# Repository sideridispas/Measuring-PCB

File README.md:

# Measuring-PCB
Voltage, Current, Temperature and Timestamped measurement board with an Atmega328 as main CPU

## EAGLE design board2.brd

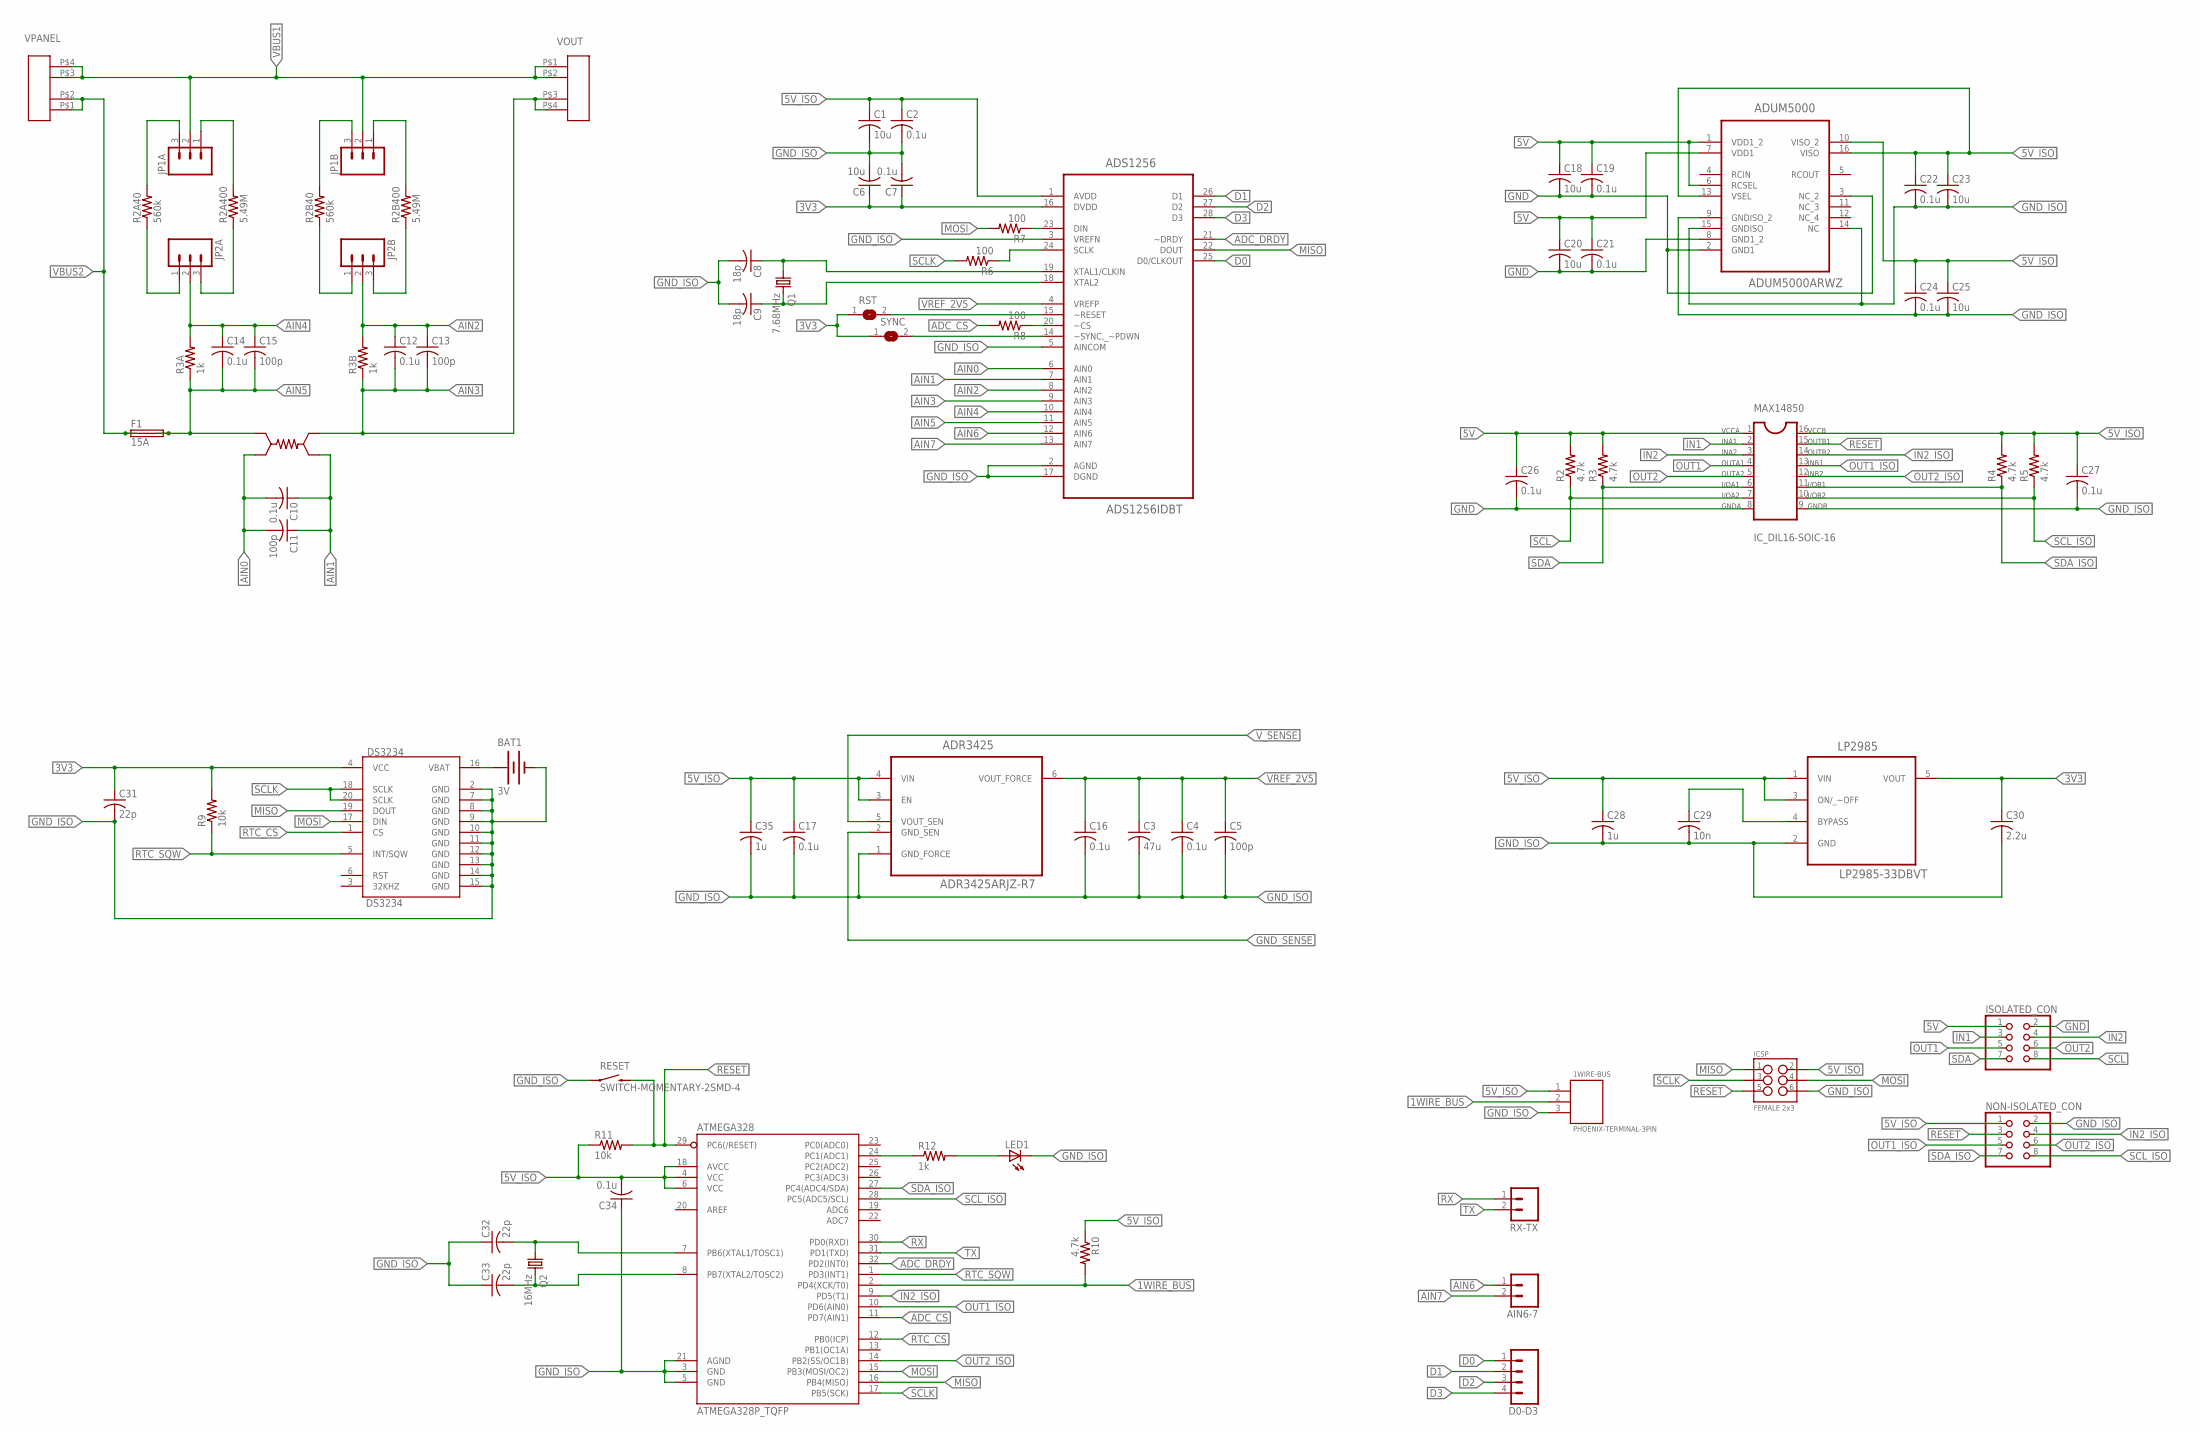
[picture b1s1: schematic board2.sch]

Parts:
1WIRE-BUS: PHOENIX-TERMINAL-3PIN
ADR3425: ADR3425ARJZ-R7; SOT95P280X145-6N
ADS1256: ADS1256IDBT; SOP65P780X200-28N
ADUM5000: ADUM5000ARWZ; SOIC127P1032X265-16N
AIN6-7: M021X02_NO_SILK; 1X02_NO_SILK
ATMEGA328: ATMEGA328P_TQFP; TQFP32-08
BAT1: 3V; BATTCON_12MM
C1, C6, C18, C20, C23, C25: 10u; C3216
C2, C4, C7, C10, C12, C14, C16, C17, C19, C21, C22, C24, C26, C27, C34: 0.1u; C3216
C3: 47u; C3216
C5, C11, C13, C15: 100p; C3216
C8, C9: 18p; C3216
C28, C35: 1u; C3216
C29: 10n; C3216
C30: 2.2u; C3216
C31, C32, C33: 22p; C3216
D0-D3: M04NO_SILK_ALL_ROUND; 1X04_NO_SILK_ALL_ROUND
DS3234: DS3234
F1: 15A; PAS_5X20
ICSP: FEMALE 2x3; 2X3
ISOLATED_CON: PINHD-2X4; 2X04
JP1A, JP1B, JP2A, JP2B: M03PTH; 1X03
LED1: LEDCHIPLED_0805; CHIPLED_0805
LP2985: LP2985-33DBVT; SOT95P280X145-5N
MAX14850: IC_DIL16-SOIC-16; SOIC-16
NON-ISOLATED_CON: PINHD-2X4; 2X04
Q1: 7.68MHz; HC49U-V
Q2: 16MHz; HC49U-V
R1: 0.005; LVK25
R2, R3, R4, R5, R10: 4.7k; R3216
R2A40, R2B40: 560k; M3216
R2A400, R2B400: 5.49M; M3216
R3A, R3B: 1k; M3216
R6, R7, R8: 100; R3216
R9, R11: 10k; R3216
R12: 1k; R3216
RESET: SWITCH-MOMENTARY-2SMD-4; TACTILE_SWITCH_TALL
RST: SJ
RX-TX: M02PTH; 1X02
SYNC: SJ
VOUT: PAS-PHOENIXTERMINAL2PIN-10.16MM; PAS-PHOENIXTERMINAL-2PIN-10.16MM
VPANEL: PAS-PHOENIXTERMINAL2PIN-10.16MM; PAS-PHOENIXTERMINAL-2PIN-10.16MM

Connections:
1WIRE_BUS: 1WIRE-BUS.2, ATMEGA328.2 (PD4(XCK/T0)), R10.2
3V3: ADS1256.16 (DVDD), C6.1, C7.1, C30.1, C31.1, DS3234.4 (VCC), LP2985.5 (VOUT), R9.2, RST.1, SYNC.1
5V: ADUM5000.1 (VDD1_2), ADUM5000.6 (RCSEL), ADUM5000.7 (VDD1), C18.1, C19.1, C20.1, C21.1, C26.1, ISOLATED_CON.1, MAX14850.1 (VCCA), R2.2, R3.2
5V_ISO: 1WIRE-BUS.1, ADR3425.3 (EN), ADR3425.4 (VIN), ADS1256.1 (AVDD), ADUM5000.10 (VISO_2), ADUM5000.13 (VSEL), ADUM5000.16 (VISO), ATMEGA328.4 (VCC), ATMEGA328.6 (VCC), ATMEGA328.18 (AVCC), C1.1, C2.1, C17.1, C22.1, C23.1, C24.1, C25.1, C27.1, C28.1, C34.2, C35.1, ICSP.2, LP2985.1 (VIN), LP2985.3 (ON/_~OFF), MAX14850.16 (VCCB), NON-ISOLATED_CON.1, R4.2, R5.2, R10.1, R11.1
ADC_CS: ATMEGA328.11 (PD7(AIN1)), R8.2
ADC_DRDY: ADS1256.21 (~DRDY), ATMEGA328.32 (PD2(INT0))
AIN0: ADS1256.6 (AIN0), C10.2, C11.2, R1.INV (2)
AIN1: ADS1256.7 (AIN1), C10.1, C11.1, R1.OUTV (4)
AIN2: ADS1256.8 (AIN2), C12.1, C13.1, JP2B.2, R3B.2
AIN3: ADS1256.9 (AIN3), C12.2, C13.2, R1.OUTI (3), R3B.1, VOUT.P$3, VOUT.P$4
AIN4: ADS1256.10 (AIN4), C14.1, C15.1, JP2A.2, R3A.2
AIN5: ADS1256.11 (AIN5), C14.2, C15.2, F1.2A, F1.2B, R1.INI (1), R3A.1
AIN6: ADS1256.12 (AIN6), AIN6-7.1
AIN7: ADS1256.13 (AIN7), AIN6-7.2
D0: ADS1256.25 (D0/CLKOUT), D0-D3.1
D1: ADS1256.26 (D1), D0-D3.2
D2: ADS1256.27 (D2), D0-D3.3
D3: ADS1256.28 (D3), D0-D3.4
GND: ADUM5000.2 (GND1), ADUM5000.3 (NC_2), ADUM5000.8 (GND1_2), C18.2, C19.2, C20.2, C21.2, C26.2, ISOLATED_CON.2, MAX14850.8 (GNDA)
GND_ISO: 1WIRE-BUS.3, ADR3425.1 (GND_FORCE), ADS1256.2 (AGND), ADS1256.3 (VREFN), ADS1256.5 (AINCOM), ADS1256.17 (DGND), ADUM5000.9 (GNDISO_2), ADUM5000.14 (NC), ADUM5000.15 (GNDISO), ATMEGA328.3 (GND), ATMEGA328.5 (GND), ATMEGA328.21 (AGND), BAT1.GND (-), C1.2, C2.2, C3.2, C4.2, C5.2, C6.2, C7.2, C8.2, C9.2, C16.2, C17.2, C22.2, C23.2, C24.2, C25.2, C27.2, C28.2, C29.2, C30.2, C31.2, C32.1, C33.1, C34.1, C35.2, DS3234.2 (GND), DS3234.7 (GND), DS3234.8 (GND), DS3234.9 (GND), DS3234.10 (GND), DS3234.11 (GND), DS3234.12 (GND), DS3234.13 (GND), DS3234.14 (GND), DS3234.15 (GND), ICSP.6, LED1.C, LP2985.2 (GND), MAX14850.9 (GNDB), NON-ISOLATED_CON.2, RESET.A2 (1)
GND_SENSE: ADR3425.2 (GND_SEN)
IN1: ISOLATED_CON.3, MAX14850.2 (INA1)
IN2: ISOLATED_CON.4, MAX14850.3 (INA2)
IN2_ISO: ATMEGA328.9 (PD5(T1)), MAX14850.14 (OUTB2), NON-ISOLATED_CON.4
MISO: ADS1256.22 (DOUT), ATMEGA328.16 (PB4(MISO)), DS3234.19 (DOUT), ICSP.1
MOSI: ATMEGA328.15 (PB3(MOSI/OC2)), DS3234.17 (DIN), ICSP.4, R7.2
unnamed: ADS1256.24 (SCLK), R6.1
unnamed: JP1A.3, R2A40.2
unnamed: JP1A.1, R2A400.2
unnamed: JP2A.3, R2A400.1
unnamed: JP2A.1, R2A40.1
unnamed: ATMEGA328.8 (PB7(XTAL2/TOSC2)), C33.2, Q2.2
unnamed: JP1B.3, R2B40.2
unnamed: JP1B.1, R2B400.2
unnamed: JP2B.3, R2B400.1
unnamed: JP2B.1, R2B40.1
unnamed: ADS1256.19 (XTAL1/CLKIN), C8.1, Q1.1
unnamed: ADS1256.18 (XTAL2), C9.1, Q1.2
unnamed: ATMEGA328.7 (PB6(XTAL1/TOSC1)), C32.2, Q2.1
unnamed: ADS1256.23 (DIN), R7.1
unnamed: BAT1.PWR@1 (+), DS3234.16 (VBAT)
unnamed: ADS1256.20 (~CS), R8.1
unnamed: ADS1256.15 (~RESET), RST.2
unnamed: ATMEGA328.24 (PC1(ADC1)), R12.1
unnamed: LED1.A, R12.2
unnamed: ADS1256.14 (~SYNC,_~PDWN), SYNC.2
unnamed: C29.1, LP2985.4 (BYPASS)
OUT1: ISOLATED_CON.5, MAX14850.4 (OUTA1)
OUT1_ISO: ATMEGA328.10 (PD6(AIN0)), MAX14850.13 (INB1), NON-ISOLATED_CON.5
OUT2: ISOLATED_CON.6, MAX14850.5 (OUTA2)
OUT2_ISO: ATMEGA328.14 (PB2(SS/OC1B)), MAX14850.12 (INB2), NON-ISOLATED_CON.6
RESET: ATMEGA328.29 (PC6(/RESET)), ICSP.5, MAX14850.15 (OUTB1), NON-ISOLATED_CON.3, R11.2, RESET.B2 (2)
RTC_CS: ATMEGA328.12 (PB0(ICP)), DS3234.1 (CS)
RTC_SQW: ATMEGA328.1 (PD3(INT1)), DS3234.5 (INT/SQW), R9.1
RX: ATMEGA328.30 (PD0(RXD)), RX-TX.1
SCL: ISOLATED_CON.8, MAX14850.7 (I/OA2), R2.1
SCLK: ATMEGA328.17 (PB5(SCK)), DS3234.18 (SCLK), DS3234.20 (SCLK), ICSP.3, R6.2
SCL_ISO: ATMEGA328.28 (PC5(ADC5/SCL)), MAX14850.10 (I/OB2), NON-ISOLATED_CON.8, R5.1
SDA: ISOLATED_CON.7, MAX14850.6 (I/OA1), R3.1
SDA_ISO: ATMEGA328.27 (PC4(ADC4/SDA)), MAX14850.11 (I/OB1), NON-ISOLATED_CON.7, R4.1
TX: ATMEGA328.31 (PD1(TXD)), RX-TX.2
VBUS1: JP1A.2, JP1B.2, VOUT.P$1, VOUT.P$2, VPANEL.P$3, VPANEL.P$4
VBUS2: F1.1A, F1.1B, VPANEL.P$1, VPANEL.P$2
VREF_2V5: ADR3425.6 (VOUT_FORCE), ADS1256.4 (VREFP), C3.1, C4.1, C5.1, C16.1
V_SENSE: ADR3425.5 (VOUT_SEN)

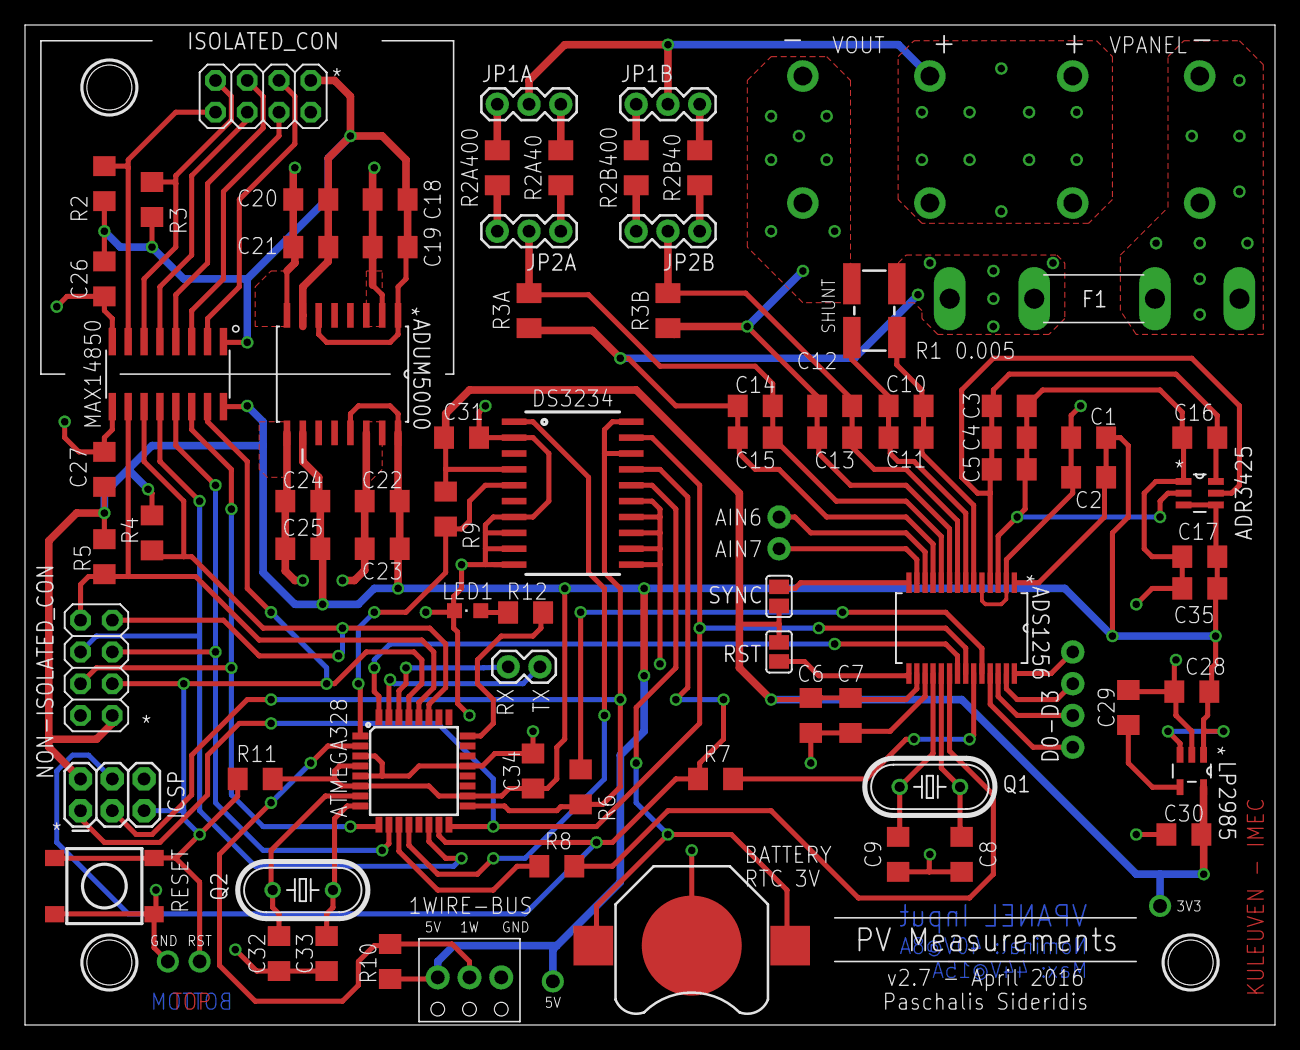
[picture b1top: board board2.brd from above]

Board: 2 copper layers, 100.0 x 80.0 mm, 81 parts (0 on the bottom side), 63 nets.

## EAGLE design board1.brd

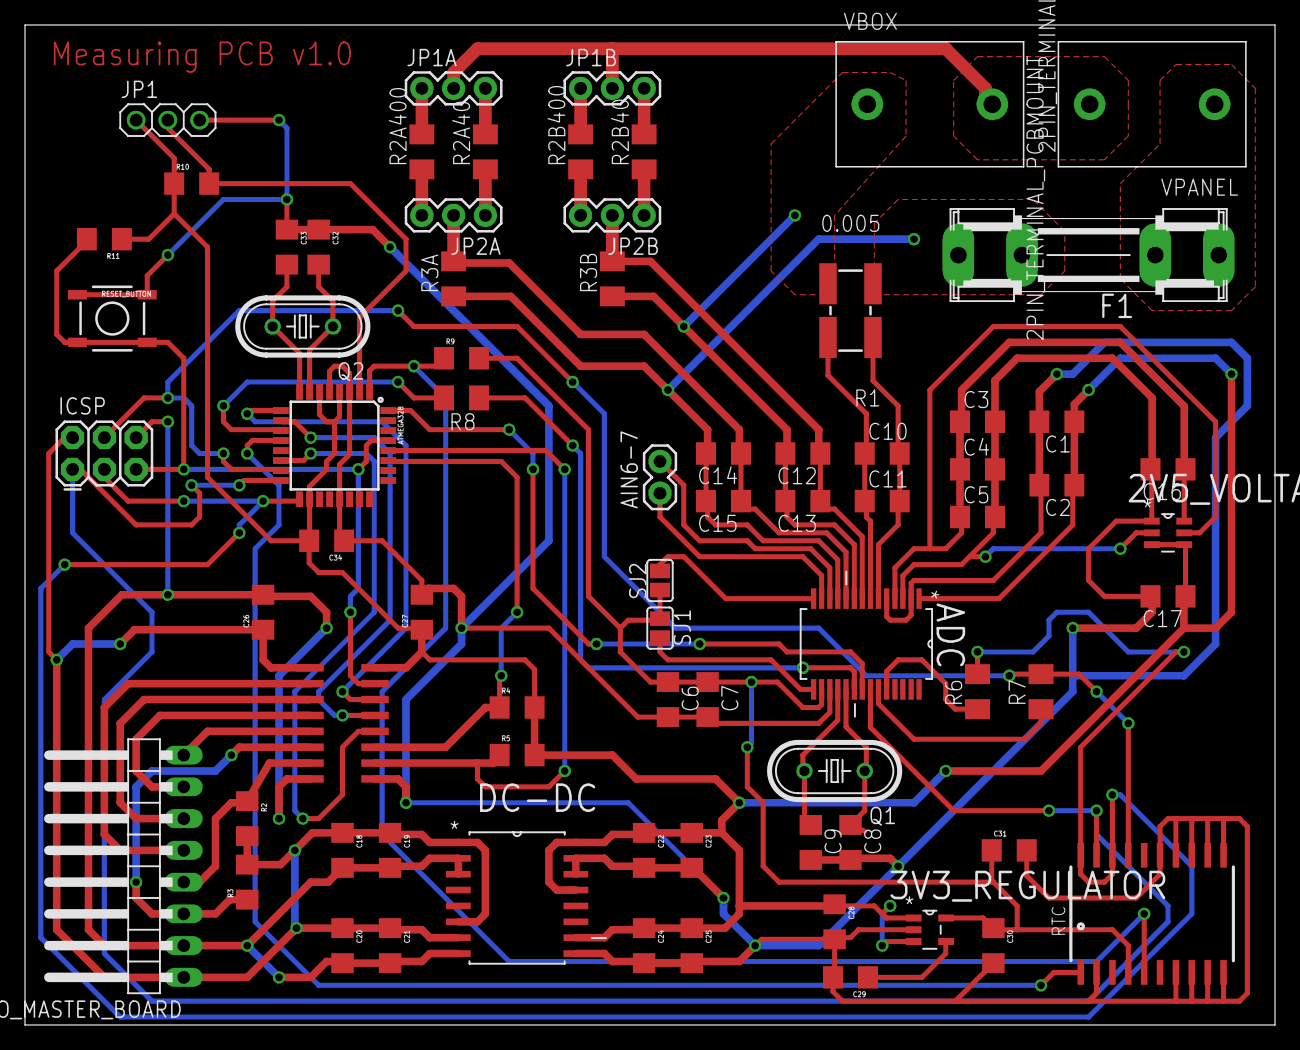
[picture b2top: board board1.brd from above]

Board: 2 copper layers, 100.0 x 80.0 mm, 74 parts (0 on the bottom side), 54 nets.

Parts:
2V5_VOLTAGE_REF: ADR3425ARJZ-R7; SOT95P280X145-6N
3V3_REGULATOR: LP2985-33DBVT; SOT95P280X145-5N
ADC: ADS1256IDBT; SOP65P780X200-28N
AIN6-7: 1X02
ATMEGA328: ATMEGA328P_TQFP; TQFP32-08
C1, C6: 10u; C3216
C2, C4, C7, C10, C12, C14, C16, C17: 0.1u; C3216
C3: 47u; C3216
C5, C11, C13, C15: 100p; C3216
C8, C9: 18p; C3216
C18, C20, C23, C25: 10u; 1206
C19, C21, C22, C24, C26, C27: 0.1u; 1206
C28: 1u; 1206
C29: 10n; 1206
C30: 2.2u; 1206
C31, C32, C33, C34: 22p; 1206
DC-DC: ADUM5000ARWZ; SOIC127P1032X265-16N
F1: 15A; SHK20L
ICSP: FEMALE 2x3; 2X3
JP1, JP1A, JP1B, JP2A, JP2B: 1X03
Q1: 7.68M; HC49U-V
Q2: 16MHz; HC49U-V
R1: 0.005; LVK25
R2, R3, R4, R5, R10: 4.7k; 1206
R2A40, R2B40: 560k; M3216
R2A400, R2B400: 5.49M; M3216
R3A, R3B: 1k; M3216
R6, R7, R8: 100; M3216
R9, R11: 10k; 1206
RESET_BUTTON: TAC_SWITCHSMD; TACTILE-SWITCH-SMD
RTC: DS3234
SIGNAL_ISOLATOR: IC_DIL16-SOIC-16; SOIC-16
SJ1, SJ2: SJ
TO_MASTER_BOARD: 1X08/90
VBOX: 2PIN_TERMINAL_PCBMOUNT; 2TERMINALBLOCK_10MMPITCH
VPANEL: 2PIN_TERMINAL_PCBMOUNT; 2TERMINALBLOCK_10MMPITCH

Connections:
1WIRE_BUS: ATMEGA328.2, JP1.2, R10.2
3V3: 3V3_REGULATOR.5, ADC.16, C6.1, C7.1, C30.1, C31.1, R9.2, RTC.4, SJ1.1, SJ2.1
5V: C18.1, C19.1, C20.1, C21.1, C26.1, DC-DC.1, DC-DC.6, DC-DC.7, ICSP.2, R2.2, R3.2, SIGNAL_ISOLATOR.1, TO_MASTER_BOARD.1
5V_ISO: 2V5_VOLTAGE_REF.3, 2V5_VOLTAGE_REF.4, 3V3_REGULATOR.1, 3V3_REGULATOR.3, ADC.1, ATMEGA328.4, ATMEGA328.6, ATMEGA328.18, C1.1, C2.1, C17.1, C22.1, C23.1, C24.1, C25.1, C27.1, C28.1, C34.2, DC-DC.10, DC-DC.13, DC-DC.16, JP1.1, R4.2, R5.2, R10.1, R11.1, SIGNAL_ISOLATOR.16
ADC_CS: ATMEGA328.11, R8.2
ADC_DRDY: ADC.21, ATMEGA328.32
AIN0: ADC.6, C10.2, C11.2, R1.INV
AIN1: ADC.7, C10.1, C11.1, R1.OUTV
AIN2: ADC.8, C12.1, C13.1, JP2B.2, R3B.2
AIN3: ADC.9, C12.2, C13.2, R1.OUTI, R3B.1, VBOX.2
AIN4: ADC.10, C14.1, C15.1, JP2A.2, R3A.2
AIN5: ADC.11, C14.2, C15.2, F1.2A, F1.2B, R1.INI, R3A.1
GND: C18.2, C19.2, C20.2, C21.2, C26.2, DC-DC.2, DC-DC.3, DC-DC.8, ICSP.6, SIGNAL_ISOLATOR.8, TO_MASTER_BOARD.2
GND_ISO: 2V5_VOLTAGE_REF.1, 2V5_VOLTAGE_REF.2, 3V3_REGULATOR.2, ADC.2, ADC.3, ADC.5, ADC.17, ATMEGA328.3, ATMEGA328.5, ATMEGA328.21, C1.2, C2.2, C3.2, C4.2, C5.2, C6.2, C7.2, C8.2, C9.2, C16.2, C17.2, C22.2, C23.2, C24.2, C25.2, C27.2, C28.2, C29.2, C30.2, C31.2, C32.1, C33.1, C34.1, DC-DC.9, DC-DC.14, DC-DC.15, JP1.3, RESET_BUTTON.1, RESET_BUTTON.2, RTC.2, RTC.7, RTC.8, RTC.9, RTC.10, RTC.11, RTC.12, RTC.13, RTC.14, RTC.15, SIGNAL_ISOLATOR.9
IN1: SIGNAL_ISOLATOR.2, TO_MASTER_BOARD.5
IN2: SIGNAL_ISOLATOR.3, TO_MASTER_BOARD.6
IN2_ISO: ATMEGA328.9, SIGNAL_ISOLATOR.14
MISO: ADC.22, ATMEGA328.16, ICSP.1, RTC.19
MOSI: ATMEGA328.15, ICSP.4, R7.2, RTC.17
unnamed: ADC.24, R6.1
unnamed: JP1A.3, R2A40.2
unnamed: JP1A.1, R2A400.2
unnamed: JP2A.3, R2A400.1
unnamed: JP2A.1, R2A40.1
unnamed: ATMEGA328.8, C33.2, Q2.2
unnamed: JP1B.3, R2B40.2
unnamed: JP1B.1, R2B400.2
unnamed: JP2B.3, R2B400.1
unnamed: JP2B.1, R2B40.1
unnamed: ADC.19, C8.1, Q1.1
unnamed: ADC.18, C9.1, Q1.2
unnamed: ATMEGA328.7, C32.2, Q2.1
unnamed: ADC.23, R7.1
unnamed: ADC.20, R8.1
unnamed: ADC.15, SJ1.2
unnamed: ADC.12, AIN6-7.2
unnamed: ADC.13, AIN6-7.1
unnamed: ADC.14, SJ2.2
unnamed: 3V3_REGULATOR.4, C29.1
OUT1: SIGNAL_ISOLATOR.4, TO_MASTER_BOARD.7
OUT1_ISO: ATMEGA328.10, SIGNAL_ISOLATOR.13
OUT2: SIGNAL_ISOLATOR.5, TO_MASTER_BOARD.8
OUT2_ISO: ATMEGA328.14, SIGNAL_ISOLATOR.12
RESET: ATMEGA328.29, ICSP.5, R11.2, RESET_BUTTON.3, RESET_BUTTON.4, SIGNAL_ISOLATOR.15
RTC_CS: ATMEGA328.12, RTC.1
RTC_SQW: ATMEGA328.1, R9.1, RTC.5
SCL: R2.1, SIGNAL_ISOLATOR.7, TO_MASTER_BOARD.4
SCLK: ATMEGA328.17, ICSP.3, R6.2, RTC.18, RTC.20
SCL_ISO: ATMEGA328.28, R5.1, SIGNAL_ISOLATOR.10
SDA: R3.1, SIGNAL_ISOLATOR.6, TO_MASTER_BOARD.3
SDA_ISO: ATMEGA328.27, R4.1, SIGNAL_ISOLATOR.11
VBUS1: JP1A.2, JP1B.2, VBOX.1, VPANEL.1
VBUS2: F1.1A, F1.1B, VPANEL.2
VREF_2V5: 2V5_VOLTAGE_REF.5, 2V5_VOLTAGE_REF.6, ADC.4, C3.1, C4.1, C5.1, C16.1

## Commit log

2016-03-04 Trying to set a new repo
2016-03-04 Created a schematic file
2016-03-04 Copied the last schematic from demo PCB
2016-03-04 Started modifying the schematic. Changed: jumpers Reset/Sync and 3v3 instead of GND, ADC package, removed R4-R5-C18, label VREFN->BEAGLE_GND
2016-03-04 Added atmega, RTC, ICSP header, Resert button. Organized the schematic with borders
2016-03-07 Added connectors, 3v3 regulator. Almost finished the schematic.
2016-03-08 Created the board and placed all the parts. No wires yet
2016-03-08 Started wiring for the first DRAFT version
2016-03-09 Almost finished the first version. I have to finish the current path and check everything
2016-03-18 finished the first draft version of the board
2016-03-18 Created board2 as version 2
2016-03-18 Version2: Placed all parts on the board. Still I have to decide about type of connectors etc and route everything
2016-03-21 Added GND planes and continue working on tracing..
2016-03-21 I think I finished routing
2016-03-21 Small details changed
2016-03-22 added battery for RTC and small changes
2016-03-22 Fixed the fuse footprint
2016-03-22 Added: connector bypassing isolation, mounting holes
2016-03-23 Finished v2.2
2016-03-23 Visual changes and clean up
2016-03-24 Added RX-TX pin jumpers. IMPORTANT: changed the 5V&GND of ICSP connector to the isolated side (after iso)
2016-03-24 Small changes
2016-03-24 No changes
2016-03-25 Added RX,TX header, D0-3 pinout. Changed the polygon shape (radius in corners). Created first try in 3D for Inventor.
2016-03-31 Footprints updated and small changes
2016-03-31 IMPORTANT: Changed the terminals for the PV connectors. They are bigger and with double connections
2016-04-05 Updated connectors and schematic. No big changes
2016-04-07 FINAL BOARD AS ORDERED - v2.7
2016-04-11 Only changes in 3D assembly

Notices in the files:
parts and their libraries:
SparkFun-Connectors: Licensing: Creative Commons ShareAlike 4.0 International - https://creativecommons.org/licenses/by-sa/4.0
